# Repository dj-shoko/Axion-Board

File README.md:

# Information
Fully functionally working PCB utilizing the RP2040 MCU with all GPIO pins broken out and able to be utilized. Main purpose of the board is for usage in beatmania IIDX and Sound Voltex controllers. The PCB can be dropped into DJ DAO based beatmania IIDX controllers as a drop in replacement, utilizing the same pin layout as their original PCBs. Main functionality allows for the usage of 11 buttons, 11 5V LEDs, 2 RGB pins, and 2 quadrature encoders (analog should also be accepted in theory due to those being hooked up to all 4 analog pins). PS2 support should be possible as well on the current PCB, but untested at the moment. Two extra pins are also available either for RGB or other general purposes if needed.

# Render and Schematics
- [Current board render](images/render.png)
- [Current board schematics](images/schematics.jpg)

# Credits
- [RP2040-designguide](https://github.com/Sleepdealr/RP2040-designguide/tree/main) to get started on the PCB designing aspects and schematics.
- [Pico Game Controller Firmware](https://github.com/speedypotato/Pico-Game-Controller) by SpeedyPotato for quick sanity check.
- [USBemani](https://github.com/progmem/usbemani) by Progmem for the current firmware I'm using for this board. Personally forked firmware UF2 files [here](https://github.com/dj-shoko/usbemani/releases).

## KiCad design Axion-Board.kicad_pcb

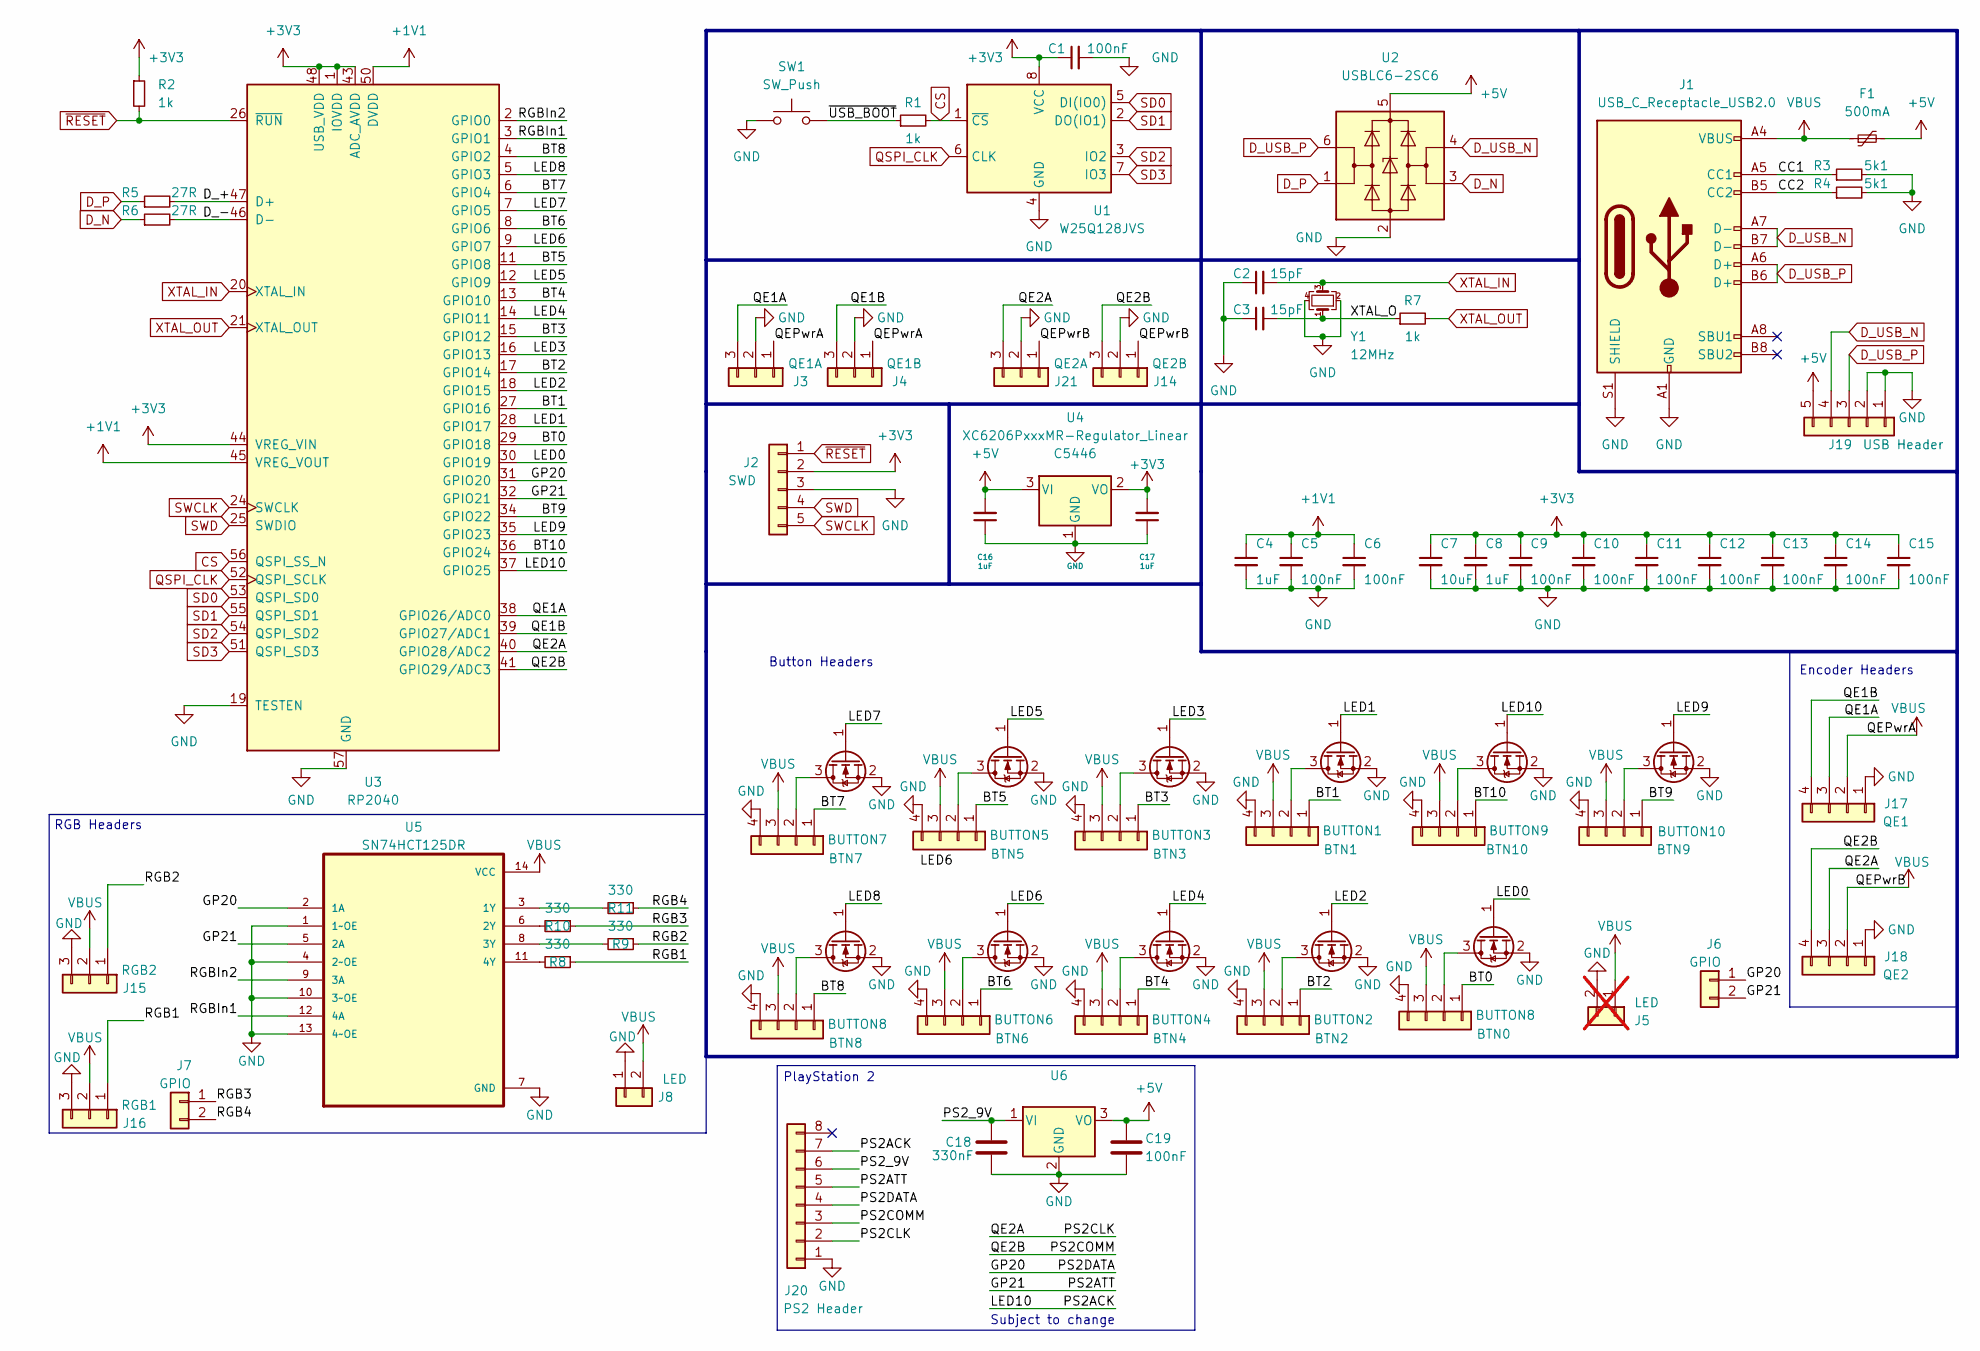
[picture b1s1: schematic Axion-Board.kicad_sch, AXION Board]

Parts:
BTN0, BTN8: BUTTON8; JST_XH_B4B-XH-A_1x04_P2.50mm_Vertical; LCSC C144395
BTN1: BUTTON1; JST_XH_B4B-XH-A_1x04_P2.50mm_Vertical; LCSC C144395
BTN2: BUTTON2; JST_XH_B4B-XH-A_1x04_P2.50mm_Vertical; LCSC C144395
BTN3: BUTTON3; JST_XH_B4B-XH-A_1x04_P2.50mm_Vertical; LCSC C144395
BTN4: BUTTON4; JST_XH_B4B-XH-A_1x04_P2.50mm_Vertical; LCSC C144395
BTN5: BUTTON5; JST_XH_B4B-XH-A_1x04_P2.50mm_Vertical; LCSC C144395
BTN6: BUTTON6; JST_XH_B4B-XH-A_1x04_P2.50mm_Vertical; LCSC C144395
BTN7: BUTTON7; JST_XH_B4B-XH-A_1x04_P2.50mm_Vertical; LCSC C144395
BTN9: BUTTON10; JST_XH_B4B-XH-A_1x04_P2.50mm_Vertical; LCSC C144395
BTN10: BUTTON9; JST_XH_B4B-XH-A_1x04_P2.50mm_Vertical; LCSC C144395
C1, C5, C6, C9, C10, C11, C12, C13, C14, C15, C19: 100nF; C_0402_1005Metric; LCSC C1525
C2, C3: 15pF; C_0402_1005Metric; LCSC C1555
C4, C8, C16, C17: 1uF; C_0402_1005Metric; LCSC C52923
C7: 10uF; C_0402_1005Metric; LCSC C15525
C18: 330nF; C_0402_1005Metric; LCSC C307420
F1: 500mA; Fuse_1206_3216Metric; LCSC C70076
J1: USB_C_Receptacle_USB2.0; USB_C_Receptacle_HRO_TYPE-C-31-M-12; LCSC C165948
J2: SWD; PinHeader_1x05_P1.27mm_Vertical
J3: QE1A; JST_XH_B3B-XH-A_1x03_P2.50mm_Vertical; LCSC C144394
J4: QE1B; JST_XH_B3B-XH-A_1x03_P2.50mm_Vertical; LCSC C144394
J5: LED; JST_XH_B2B-XH-A_1x02_P2.50mm_Vertical; LCSC C158012; not fitted
J6, J7: GPIO; PinHeader_1x02_P1.27mm_Vertical
J8: LED; JST_XH_B2B-XH-A_1x02_P2.50mm_Vertical; LCSC C158012
J14: QE2B; JST_XH_B3B-XH-A_1x03_P2.50mm_Vertical; LCSC C144394
J15: RGB2; JST_XH_B3B-XH-A_1x03_P2.50mm_Vertical; LCSC C144394
J16: RGB1; JST_XH_B3B-XH-A_1x03_P2.50mm_Vertical; LCSC C144394
J17: QE1; JST_XH_B4B-XH-A_1x04_P2.50mm_Vertical; LCSC C144395
J18: QE2; JST_XH_B4B-XH-A_1x04_P2.50mm_Vertical; LCSC C144395
J19: USB Header; JST_XH_B5B-XH-A_1x05_P2.50mm_Vertical; LCSC C157991
J20: PS2 Header; RJ45_OST_PJ012-8P8CX_Vertical; LCSC C2902702
J21: QE2A; JST_XH_B3B-XH-A_1x03_P2.50mm_Vertical; LCSC C144394
Q1, Q2, Q3, Q4, Q5, Q6, Q7, Q8, Q9, Q10, Q11: BSS138; SOT-23; LCSC C112239
R1, R2, R7: 1k; R_0402_1005Metric; LCSC C11702
R3, R4: 5k1; R_0402_1005Metric; LCSC C25905
R5, R6: 27R; R_0603_1608Metric; LCSC C25190
R8, R9, R10, R11: 330; R_0402_1005Metric; LCSC C12246
SW1: SW_Push; SW_SPST_PTS810; LCSC C221895
U1: W25Q128JVS; SOIC-8_5.23x5.23mm_P1.27mm; LCSC C131025
U2: USBLC6-2SC6; SOT-23-6; LCSC C2827654
U3: RP2040; RP2040-QFN-56; LCSC C2040
U4: XC6206PxxxMR-Regulator_Linear; SOT-23; LCSC C5446
U5: SN74HCT125DR; LCSC C352957
U6: 78M05_TO252-3; TO-252-2; LCSC C347278
Y1: 12MHz; Crystal_SMD_3225-4Pin_3.2x2.5mm; LCSC C9002

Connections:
+1V1: C4.1, C5.1, C6.1, U3.23 (DVDD), U3.45 (VREG_VOUT), U3.50 (DVDD)
+3V3: C1.1, C7.1, C8.1, C9.1, C10.1, C11.1, C12.1, C13.1, C14.1, C15.1, C17.2, J2.2, R2.1, U1.8 (VCC), U3.1 (IOVDD), U3.10 (IOVDD), U3.22 (IOVDD), U3.33 (IOVDD), U3.42 (IOVDD), U3.43 (ADC_AVDD), U3.44 (VREG_VIN), U3.48 (USB_VDD), U3.49 (IOVDD), U4.2 (VO)
+5V: C16.2, C19.1, F1.2, J19.5, U2.5 (VBUS), U4.3 (VI), U6.3 (VO)
/BT0: BTN0.1, U3.29 (GPIO18)
/BT1: BTN1.1, U3.27 (GPIO16)
/BT2: BTN2.1, U3.17 (GPIO14)
/BT3: BTN3.1, U3.15 (GPIO12)
/BT4: BTN4.1, U3.13 (GPIO10)
/BT5: BTN5.1, U3.11 (GPIO8)
/BT6: BTN6.1, U3.8 (GPIO6)
/BT7: BTN7.1, U3.6 (GPIO4)
/BT8: BTN8.1, U3.4 (GPIO2)
/BT9: BTN9.1, U3.34 (GPIO22)
/BT10: BTN10.1, U3.36 (GPIO24)
/CC1: J1.A5 (CC1), R3.1
/CC2: J1.B5 (CC2), R4.1
/D_+: R5.2, U3.47 (D+)
/D_-: R6.2, U3.46 (D-)
/GP20: J6.1, J20.4, U3.31 (GPIO20), U5.2 (1A)
/GP21: J6.2, J20.5, U3.32 (GPIO21), U5.5 (2A)
/LED0: Q5.1 (G), U3.30 (GPIO19)
/LED1: Q8.1 (G), U3.28 (GPIO17)
/LED2: Q4.1 (G), U3.18 (GPIO15)
/LED3: Q9.1 (G), U3.16 (GPIO13)
/LED4: Q2.1 (G), U3.14 (GPIO11)
/LED5: Q10.1 (G), U3.12 (GPIO9)
/LED6: Q1.1 (G), U3.9 (GPIO7)
/LED7: Q11.1 (G), U3.7 (GPIO5)
/LED8: Q3.1 (G), U3.5 (GPIO3)
/LED9: Q6.1 (G), U3.35 (GPIO23)
/LED10: J20.7, Q7.1 (G), U3.37 (GPIO25)
/PS2CLK: J18.3, J20.2, J21.3, U3.40 (GPIO28/ADC2)
/PS2COMM: J14.3, J18.4, J20.3, U3.41 (GPIO29/ADC3)
/PS2_9V: C18.1, J20.6, U6.1 (VI)
/QE1A: J3.3, J17.3, U3.38 (GPIO26/ADC0)
/QE1B: J4.3, J17.4, U3.39 (GPIO27/ADC1)
/RGB1: J16.1, R8.1
/RGB2: J15.1, R9.1
/RGB3: J7.1, R10.1
/RGB4: J7.2, R11.1
/RGBIn1: U3.3 (GPIO1), U5.12 (4A)
/RGBIn2: U3.2 (GPIO0), U5.9 (3A)
/XTAL_O: C3.2, R7.1, Y1.1
/~USB_BOOT: R1.1, SW1.2
CS: R1.2, U1.1 (~CS), U3.56 (QSPI_SS_N)
D_N: R6.1, U2.3 (I/O2)
D_P: R5.1, U2.1 (I/O1)
D_USB_N: J1.A7 (D-), J1.B7 (D-), J19.4, U2.4 (I/O2)
D_USB_P: J1.A6 (D+), J1.B6 (D+), J19.3, U2.6 (I/O1)
GND: BTN0.4, BTN1.4, BTN2.4, BTN3.4, BTN4.4, BTN5.4, BTN6.4, BTN7.4, BTN8.4, BTN9.4, BTN10.4, C1.2, C2.1, C3.1, C4.2, C5.2, C6.2, C7.2, C8.2, C9.2, C10.2, C11.2, C12.2, C13.2, C14.2, C15.2, C16.1, C17.1, C18.2, C19.2, J1.A1 (GND), J1.A12 (GND), J1.S1 (SHIELD), J2.3, J3.2, J4.2, J5.2, J8.1, J14.2, J15.3, J16.3, J17.1, J18.1, J19.1, J19.2, J20.1, J21.2, Q1.2 (S), Q2.2 (S), Q3.2 (S), Q4.2 (S), Q5.2 (S), Q6.2 (S), Q7.2 (S), Q8.2 (S), Q9.2 (S), Q10.2 (S), Q11.2 (S), R3.2, R4.2, SW1.1, U1.4 (GND), U2.2 (GND), U3.19 (TESTEN), U3.57 (GND), U4.1 (GND), U5.1 (1~OE), U5.4 (2~OE), U5.7 (GND), U5.10 (3~OE), U5.13 (4~OE), U6.2 (GND), Y1.2, Y1.4; also elsewhere on the board
unnamed: BTN0.2, Q5.3 (D)
unnamed: BTN1.2, Q8.3 (D)
unnamed: BTN2.2, Q4.3 (D)
unnamed: BTN3.2, Q9.3 (D)
unnamed: BTN4.2, Q2.3 (D)
unnamed: BTN5.2, Q10.3 (D)
unnamed: BTN6.2, Q1.3 (D)
unnamed: BTN7.2, Q11.3 (D)
unnamed: BTN8.2, Q3.3 (D)
unnamed: BTN9.2, Q6.3 (D)
unnamed: BTN10.2, Q7.3 (D)
unnamed: R11.2, U5.3 (1Y)
unnamed: R10.2, U5.6 (2Y)
unnamed: R9.2, U5.8 (3Y)
unnamed: R8.2, U5.11 (4Y)
QSPI_CLK: U1.6 (CLK), U3.52 (QSPI_SCLK)
SD0: U1.5 (DI(IO0)), U3.53 (QSPI_SD0)
SD1: U1.2 (DO(IO1)), U3.55 (QSPI_SD1)
SD2: U1.3 (IO2), U3.54 (QSPI_SD2)
SD3: U1.7 (IO3), U3.51 (QSPI_SD3)
SWCLK: J2.5, U3.24 (SWCLK)
SWD: J2.4, U3.25 (SWDIO)
VBUS: BTN0.3, BTN1.3, BTN2.3, BTN3.3, BTN4.3, BTN5.3, BTN6.3, BTN7.3, BTN8.3, BTN9.3, BTN10.3, F1.1, J1.A4 (VBUS), J1.A9 (VBUS), J1.B4 (VBUS), J1.B9 (VBUS), J3.1, J4.1, J5.1, J8.2, J14.1, J15.2, J16.2, J17.2, J18.2, J21.1, U5.14 (VCC); also elsewhere on the board
XTAL_IN: C2.2, U3.20 (XTAL_IN), Y1.3
XTAL_OUT: R7.2, U3.21 (XTAL_OUT)
~RESET: J2.1, R2.2, U3.26 (~RUN)

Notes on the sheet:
Button Headers
PlayStation 2
RGB Headers
Subject to change
Encoder Headers

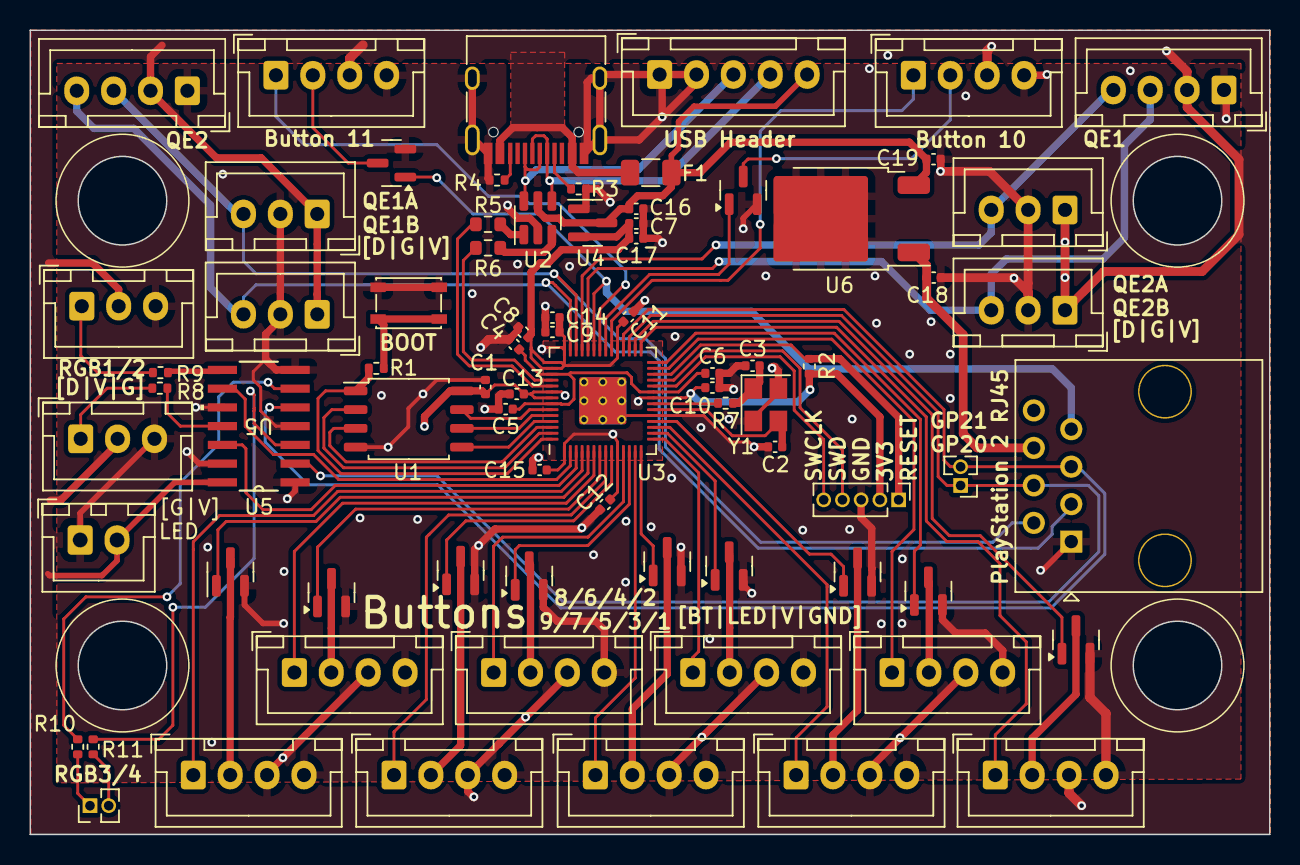
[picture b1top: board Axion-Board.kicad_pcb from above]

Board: 2 copper layers, 84.0 x 54.5 mm, 76 parts (0 on the bottom side), 76 nets.

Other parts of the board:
LED: LED; JST_XH_B2B-XH-A_1x02_P2.50mm_Vertical

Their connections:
GND: LED.1; also elsewhere on the board
VBUS: LED.2; also elsewhere on the board

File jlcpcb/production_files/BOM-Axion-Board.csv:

Comment,Designator,Footprint,LCSC
BSS138,"Q1,Q10,Q11,Q2,Q3,Q4,Q5,Q6,Q7,Q8,Q9",SOT-23,C112239
1k,"R1,R2,R7",R_0402_1005Metric,C11702
330,"R10,R11,R8,R9",R_0402_1005Metric,C12246
W25Q128JVS,U1,SOIC-8_5.23x5.23mm_P1.27mm,C131025
QE2B,"J14,J15,J16,J21,J3,J4",JST_XH_B3B-XH-A_1x03_P2.50mm_Vertical,C144394
BUTTON8,"BTN0,BTN1,BTN10,BTN2,BTN3,BTN4,BTN5,BTN6,BTN7,BTN8,BTN9,J17,J18",JST_XH_B4B-XH-A_1x04_P2.50mm_Vertical,C144395
100nF,"C1,C10,C11,C12,C13,C14,C15,C19,C5,C6,C9",C_0402_1005Metric,C1525
10uF,C7,C_0402_1005Metric,C15525
15pF,"C2,C3",C_0402_1005Metric,C1555
USB Header,J19,JST_XH_B5B-XH-A_1x05_P2.50mm_Vertical,C157991
USB_C_Receptacle_USB2.0,J1,USB_C_Receptacle_HRO_TYPE-C-31-M-12,C165948
RP2040,U3,RP2040-QFN-56,C2040
SW_Push,SW1,SW_SPST_PTS810,C221895
27R,"R5,R6",R_0603_1608Metric,C25190
5k1,"R3,R4",R_0402_1005Metric,C25905
USBLC6-2SC6,U2,SOT-23-6,C2827654
PS2 Header,J20,RJ45_OST_PJ012-8P8CX_Vertical,C2902702
330nF,C18,C_0402_1005Metric,C307420
78M05_TO252-3,U6,TO-252-2,C347278
SN74HCT125DR,U5,SN74HCT125DR,C352957
1uF,"C16,C17,C4,C8",C_0402_1005Metric,C52923
XC6206PxxxMR-Regulator_Linear,U4,SOT-23,C5446
500mA,F1,Fuse_1206_3216Metric,C70076
12MHz,Y1,Crystal_SMD_3225-4Pin_3.2x2.5mm,C9002

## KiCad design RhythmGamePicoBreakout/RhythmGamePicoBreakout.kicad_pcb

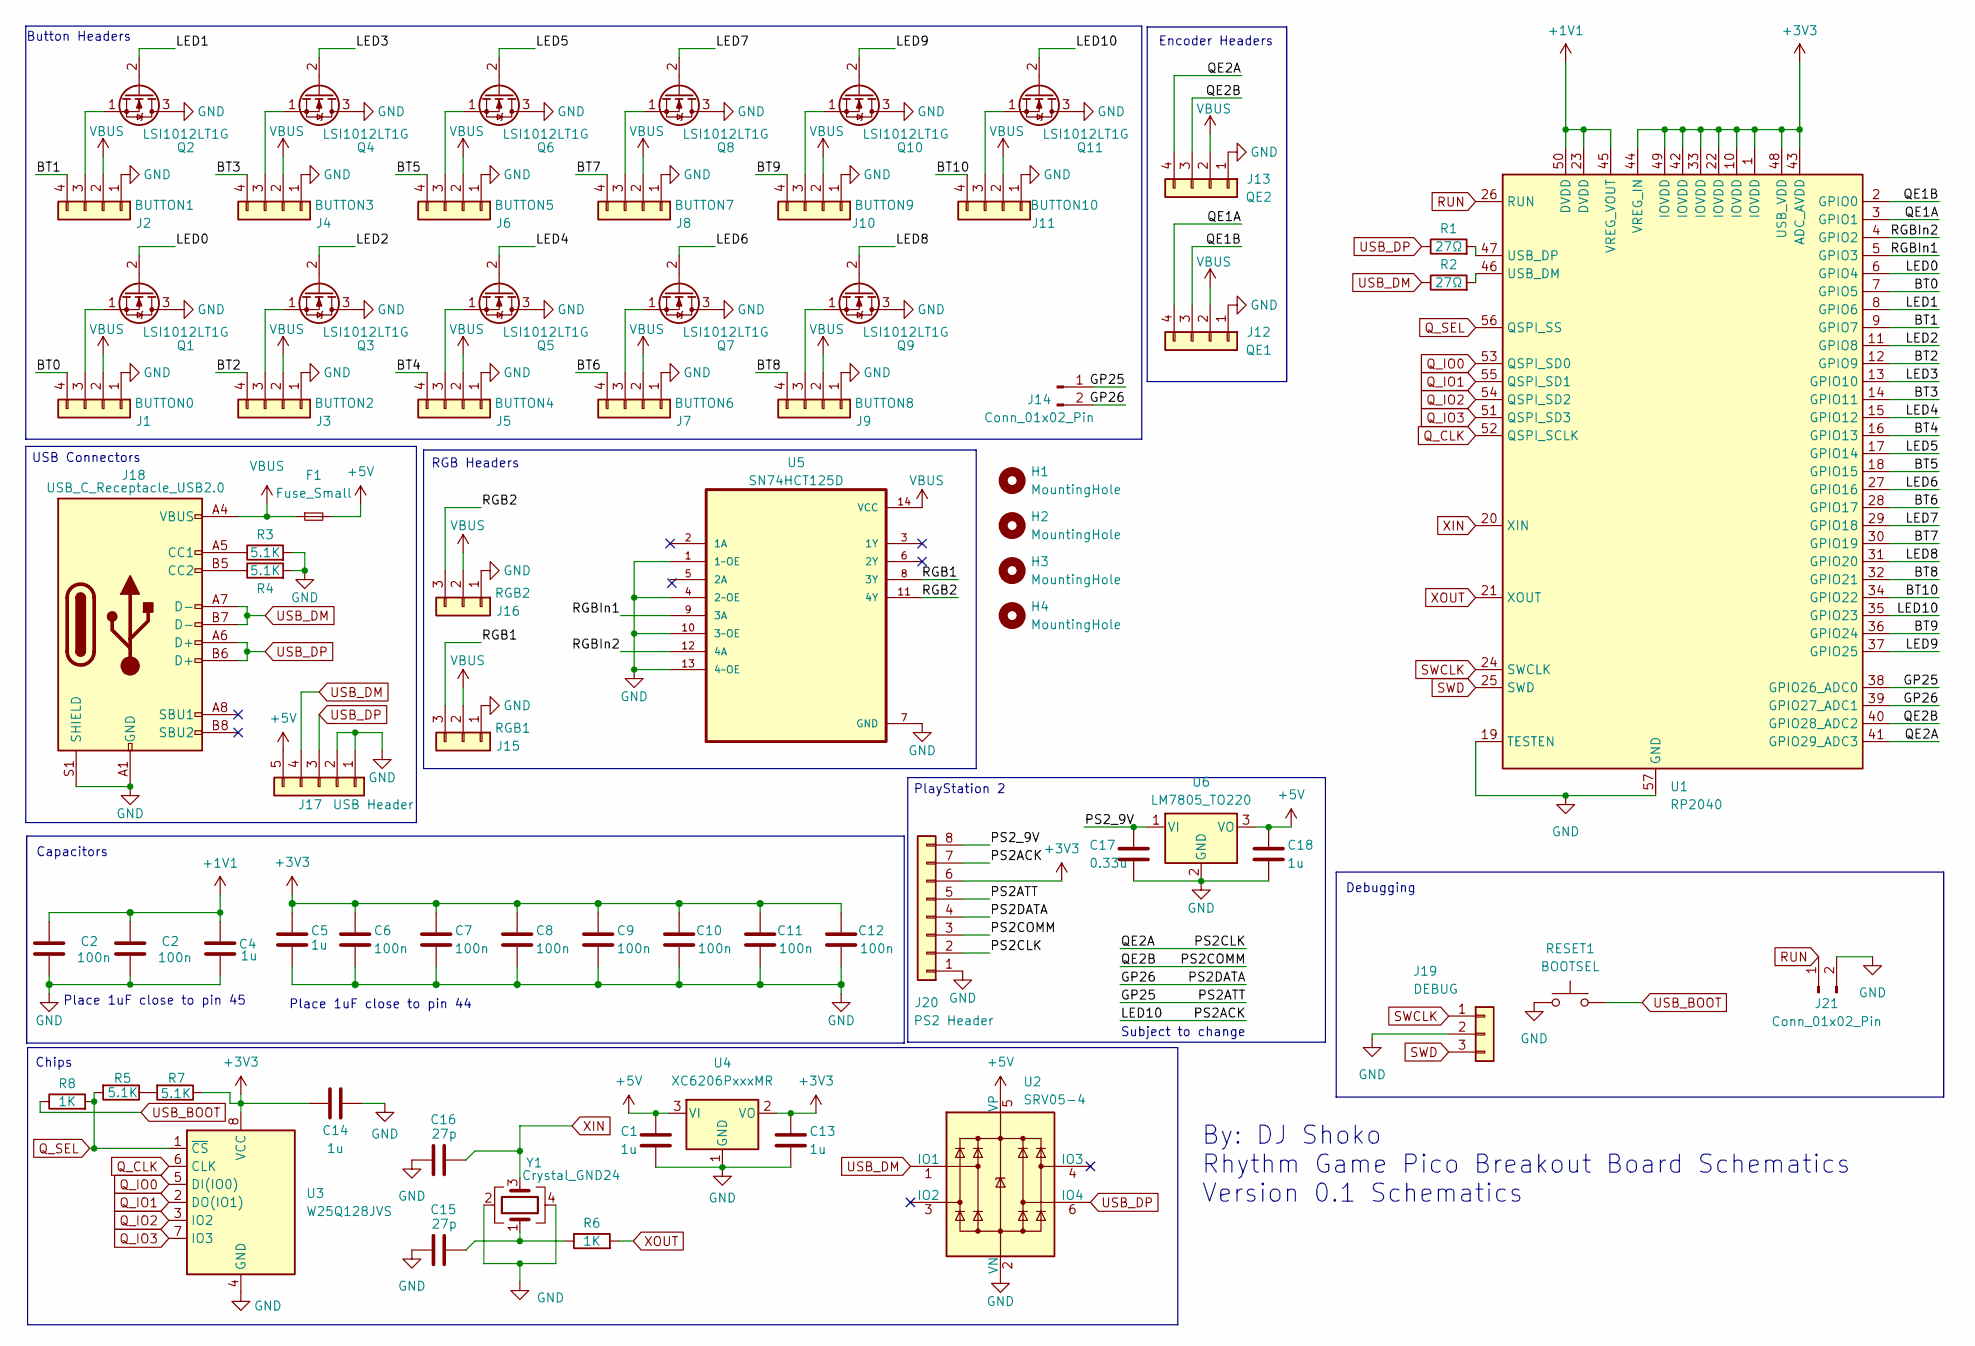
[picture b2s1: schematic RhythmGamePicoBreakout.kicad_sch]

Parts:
C1, C4, C5, C13, C14, C18: 1u; C_0402_1005Metric_Pad0.74x0.62mm_HandSolder
C2, C6, C7, C8, C9, C10, C11, C12: 100n; C_0402_1005Metric_Pad0.74x0.62mm_HandSolder
C15, C16: 27p; C_0402_1005Metric_Pad0.74x0.62mm_HandSolder
C17: 0.33u; C_0402_1005Metric_Pad0.74x0.62mm_HandSolder
F1: Fuse_Small; C_0402_1005Metric_Pad0.74x0.62mm_HandSolder
H1, H2, H3, H4: MountingHole; MountingHole_3.7mm
J1: BUTTON0; JST_XH_B4B-XH-AM_1x04_P2.50mm_Vertical
J2: BUTTON1; JST_XH_B4B-XH-AM_1x04_P2.50mm_Vertical
J3: BUTTON2; JST_XH_B4B-XH-AM_1x04_P2.50mm_Vertical
J4: BUTTON3; JST_XH_B4B-XH-AM_1x04_P2.50mm_Vertical
J5: BUTTON4; JST_XH_B4B-XH-AM_1x04_P2.50mm_Vertical
J6: BUTTON5; JST_XH_B4B-XH-AM_1x04_P2.50mm_Vertical
J7: BUTTON6; JST_XH_B4B-XH-AM_1x04_P2.50mm_Vertical
J8: BUTTON7; JST_XH_B4B-XH-AM_1x04_P2.50mm_Vertical
J9: BUTTON8; JST_XH_B4B-XH-AM_1x04_P2.50mm_Vertical
J10: BUTTON9; JST_XH_B4B-XH-AM_1x04_P2.50mm_Vertical
J11: BUTTON10; JST_XH_B4B-XH-AM_1x04_P2.50mm_Vertical
J12: QE1; JST_XH_B4B-XH-AM_1x04_P2.50mm_Vertical
J13: QE2; JST_XH_B4B-XH-AM_1x04_P2.50mm_Vertical
J14, J21: Conn_01x02_Pin; PinSocket_1x02_P2.00mm_Vertical
J15: RGB1; JST_XH_B3B-XH-AM_1x03_P2.50mm_Vertical
J16: RGB2; JST_XH_B3B-XH-AM_1x03_P2.50mm_Vertical
J17: USB Header; JST_XH_B5B-XH-AM_1x05_P2.50mm_Vertical
J18: USB_C_Receptacle_USB2.0; USB_C_Receptacle_GCT_USB4085
J19: DEBUG; PinHeader_1x03_P2.00mm_Vertical
J20: PS2 Header; JST_XH_B8B-XH-AM_1x08_P2.50mm_Vertical
Q1, Q2, Q3, Q4, Q5, Q6, Q7, Q8, Q9, Q10, Q11: LSI1012LT1G; SOT-23
R1, R2: 27Ω; R_0402_1005Metric_Pad0.72x0.64mm_HandSolder
R3, R4, R5, R7: 5.1K; R_0402_1005Metric_Pad0.72x0.64mm_HandSolder
R6, R8: 1K; R_0402_1005Metric_Pad0.72x0.64mm_HandSolder
RESET1: BOOTSEL; SW_Push_1P1T_NO_CK_KSC6xxJ
U1: RP2040; QFN-56-1EP_7x7mm_P0.4mm_EP3.2x3.2mm
U2: SRV05-4; SOT-23-6
U3: W25Q128JVS; SOIC-8_5.23x5.23mm_P1.27mm
U4: XC6206PxxxMR; SOT-23-3
U5: SN74HCT125D; SOIC127P600X175-14N
U6: LM7805_TO220; TO-220-3_Vertical
Y1: Crystal_GND24; Crystal_SMD_3225-4Pin_3.2x2.5mm_HandSoldering

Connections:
+1V1: C2.1, C4.1, U1.23 (DVDD), U1.45 (VREG_VOUT), U1.50 (DVDD); also elsewhere on the board
+3V3: C5.1, C6.1, C7.1, C8.1, C9.1, C10.1, C11.1, C12.1, C13.1, C14.2, J20.6, R7.1, U1.1 (IOVDD), U1.10 (IOVDD), U1.22 (IOVDD), U1.33 (IOVDD), U1.42 (IOVDD), U1.43 (ADC_AVDD), U1.44 (VREG_IN), U1.48 (USB_VDD), U1.49 (IOVDD), U3.8 (VCC), U4.2 (VO)
+5V: C1.1, C18.1, F1.2, J17.5, U2.5 (VP), U4.3 (VI), U6.3 (VO)
/BT0: J1.4, U1.7 (GPIO5)
/BT1: J2.4, U1.9 (GPIO7)
/BT2: J3.4, U1.12 (GPIO9)
/BT3: J4.4, U1.14 (GPIO11)
/BT4: J5.4, U1.16 (GPIO13)
/BT5: J6.4, U1.18 (GPIO15)
/BT6: J7.4, U1.28 (GPIO17)
/BT7: J8.4, U1.30 (GPIO19)
/BT8: J9.4, U1.32 (GPIO21)
/BT9: J10.4, U1.36 (GPIO24)
/BT10: J11.4, U1.34 (GPIO22)
/GP25: J14.1, J20.5, U1.38 (GPIO26_ADC0)
/GP26: J14.2, J20.4, U1.39 (GPIO27_ADC1)
/LED0: Q1.2 (G), U1.6 (GPIO4)
/LED1: Q2.2 (G), U1.8 (GPIO6)
/LED2: Q3.2 (G), U1.11 (GPIO8)
/LED3: Q4.2 (G), U1.13 (GPIO10)
/LED4: Q5.2 (G), U1.15 (GPIO12)
/LED5: Q6.2 (G), U1.17 (GPIO14)
/LED6: Q7.2 (G), U1.27 (GPIO16)
/LED7: Q8.2 (G), U1.29 (GPIO18)
/LED8: Q9.2 (G), U1.31 (GPIO20)
/LED9: Q10.2 (G), U1.37 (GPIO25)
/LED10: J20.7, Q11.2 (G), U1.35 (GPIO23)
/PS2CLK: J13.4, J20.2, U1.41 (GPIO29_ADC3)
/PS2COMM: J13.3, J20.3, U1.40 (GPIO28_ADC2)
/PS2_9V: C17.1, J20.8, U6.1 (VI)
/QE1A: J12.4, U1.3 (GPIO1)
/QE1B: J12.3, U1.2 (GPIO0)
/RGB1: J15.3, U5.8 (3Y)
/RGB2: J16.3, U5.11 (4Y)
/RGBIn1: U1.5 (GPIO3), U5.9 (3A)
/RGBIn2: U1.4 (GPIO2), U5.12 (4A)
GND: C1.2, C2.2, C4.2, C5.2, C6.2, C7.2, C8.2, C9.2, C10.2, C11.2, C12.2, C13.2, C14.1, C15.1, C16.1, C17.2, C18.2, J1.1, J2.1, J3.1, J4.1, J5.1, J6.1, J7.1, J8.1, J9.1, J10.1, J11.1, J12.1, J13.1, J15.1, J16.1, J17.1, J17.2, J18.A1 (GND), J18.A12 (GND), J18.B1 (GND), J18.B12 (GND), J18.S1 (SHIELD), J19.2, J20.1, J21.2, Q1.3 (D), Q2.3 (D), Q3.3 (D), Q4.3 (D), Q5.3 (D), Q6.3 (D), Q7.3 (D), Q8.3 (D), Q9.3 (D), Q10.3 (D), Q11.3 (D), R3.2, R4.2, RESET1.1, U1.19 (TESTEN), U1.57 (GND), U2.2 (VN), U3.4 (GND), U4.1 (GND), U5.1 (1~OE), U5.4 (2~OE), U5.7 (GND), U5.10 (3~OE), U5.13 (4~OE), U6.2 (GND), Y1.2, Y1.4; also elsewhere on the board
unnamed: C15.2, R6.1, Y1.1
unnamed: J1.3, Q1.1 (S)
unnamed: J2.3, Q2.1 (S)
unnamed: J3.3, Q3.1 (S)
unnamed: J4.3, Q4.1 (S)
unnamed: J5.3, Q5.1 (S)
unnamed: J6.3, Q6.1 (S)
unnamed: J7.3, Q7.1 (S)
unnamed: J8.3, Q8.1 (S)
unnamed: J9.3, Q9.1 (S)
unnamed: J10.3, Q10.1 (S)
unnamed: J11.3, Q11.1 (S)
unnamed: J18.A5 (CC1), R3.1
unnamed: J18.B5 (CC2), R4.1
unnamed: R5.1, R7.2
unnamed: R2.2, U1.46 (USB_DM)
unnamed: R1.2, U1.47 (USB_DP)
Q_CLK: U1.52 (QSPI_SCLK), U3.6 (CLK)
Q_IO0: U1.53 (QSPI_SD0), U3.5 (DI(IO0))
Q_IO1: U1.55 (QSPI_SD1), U3.2 (DO(IO1))
Q_IO2: U1.54 (QSPI_SD2), U3.3 (IO2)
Q_IO3: U1.51 (QSPI_SD3), U3.7 (IO3)
Q_SEL: R5.2, R8.2, U1.56 (QSPI_SS), U3.1 (~CS)
RUN: J21.1, U1.26 (RUN)
SWCLK: J19.1, U1.24 (SWCLK)
SWD: J19.3, U1.25 (SWD)
USB_BOOT: R8.1, RESET1.2
USB_DM: J17.4, J18.A7 (D-), J18.B7 (D-), R2.1, U2.1 (IO1)
USB_DP: J17.3, J18.A6 (D+), J18.B6 (D+), R1.1, U2.6 (IO4)
VBUS: F1.1, J1.2, J2.2, J3.2, J4.2, J5.2, J6.2, J7.2, J8.2, J9.2, J10.2, J11.2, J12.2, J13.2, J15.2, J16.2, J18.A4 (VBUS), J18.A9 (VBUS), J18.B4 (VBUS), J18.B9 (VBUS), U5.14 (VCC)
XIN: C16.2, U1.20 (XIN), Y1.3
XOUT: R6.2, U1.21 (XOUT)

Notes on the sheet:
PlayStation 2
USB Connectors
By: DJ Shoko Rhythm Game Pico Breakout Board Schematics Version 0.1 Schematics
Capacitors
Subject to change
Encoder Headers
Place 1uF close to pin 44
RGB Headers
Chips
Button Headers
Place 1uF close to pin 45
Debugging

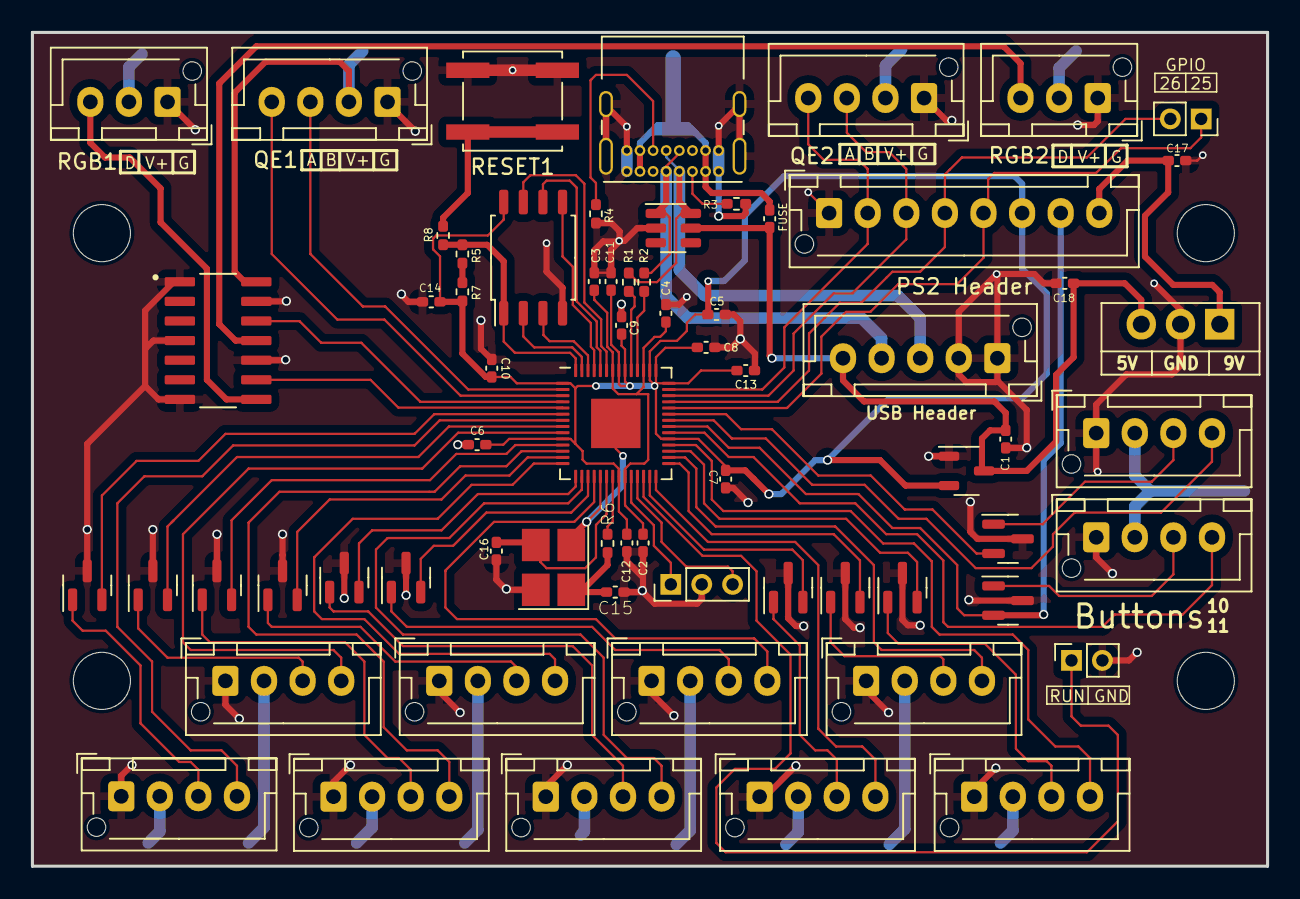
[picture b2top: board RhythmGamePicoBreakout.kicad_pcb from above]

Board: 2 copper layers, 80.0 x 54.0 mm, 71 parts (0 on the bottom side), 69 nets.

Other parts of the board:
C3: 100n; C_0402_1005Metric_Pad0.74x0.62mm_HandSolder

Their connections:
+1V1: C3.1; also elsewhere on the board
GND: C3.2; also elsewhere on the board

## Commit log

2023-06-25 Add files via upload
    Initial commit
2023-06-30 Updated Schematics and PCB design
2023-06-30 Updated Schematics image and PCB render
2023-06-30 Updated Render
2023-07-01 Updated schematics and completely redone tracing
2023-07-01 Updated renders
2023-07-01 Completely redid the traces
2024-03-02 Redid entire board and renamed project.
2024-11-20 Fixed the mosfet wiring
2024-11-20 Updated JLCPCB files
2024-11-20 Latest JLCPCB Gerber Files
2024-11-30 Added turntable LED header
2024-11-30 Added turntable LED header with BOM part
2024-11-30 Added newest render
